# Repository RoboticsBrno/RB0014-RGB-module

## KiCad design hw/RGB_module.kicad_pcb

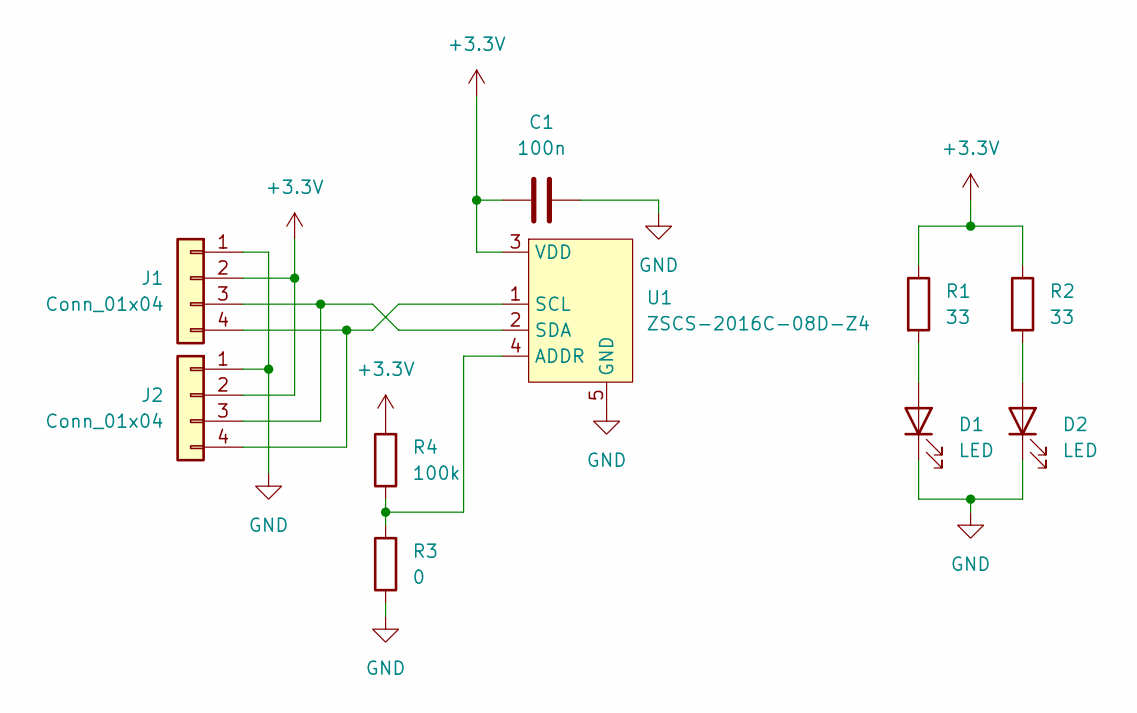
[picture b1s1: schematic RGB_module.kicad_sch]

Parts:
C1: 100n; C_0402_1005Metric; LCSC C1525
D1, D2: LED; XL-3014UWC-02; LCSC C2843791
J1, J2: Conn_01x04; JST_SH_BM04B-SRSS-TB_1x04-1MP_P1.00mm_Vertical; LCSC C7433440
R1, R2: 33; R_0603_1608Metric; LCSC C23140
R3: 0; R_0603_1608Metric_Pad0.98x0.95mm_HandSolder; LCSC C2907080
R4: 100k; R_0603_1608Metric_Pad0.98x0.95mm_HandSolder; LCSC C2907088
U1: ZSCS-2016C-08D-Z4; LCSC C5337482

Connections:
+3.3V: C1.1, J1.2, J2.2, R1.1, R2.1, R4.2, U1.3 (VDD)
GND: C1.2, D1.1 (K), D2.1 (K), J1.1, J2.1, R3.1, U1.5 (GND)
unnamed: D1.2 (A), R1.2
unnamed: D2.2 (A), R2.2
unnamed: J1.3, J2.3, U1.2 (SDA)
unnamed: J1.4, J2.4, U1.1 (SCL)
unnamed: R3.2, R4.1, U1.4 (ADDR)

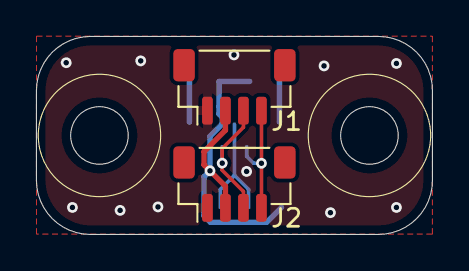
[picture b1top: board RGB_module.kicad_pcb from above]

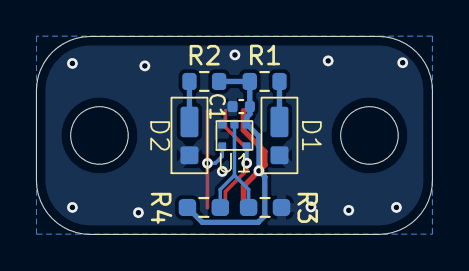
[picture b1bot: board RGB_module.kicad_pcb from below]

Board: 2 copper layers, 22.0 x 11.0 mm, 10 parts (8 on the bottom side), 7 nets.

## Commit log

2025-05-23 files created
2025-05-23 board_v1
2025-05-26 board_v2
2025-05-27 board_v3
2025-05-27 PCB_update
2025-05-27 added PCB panel
